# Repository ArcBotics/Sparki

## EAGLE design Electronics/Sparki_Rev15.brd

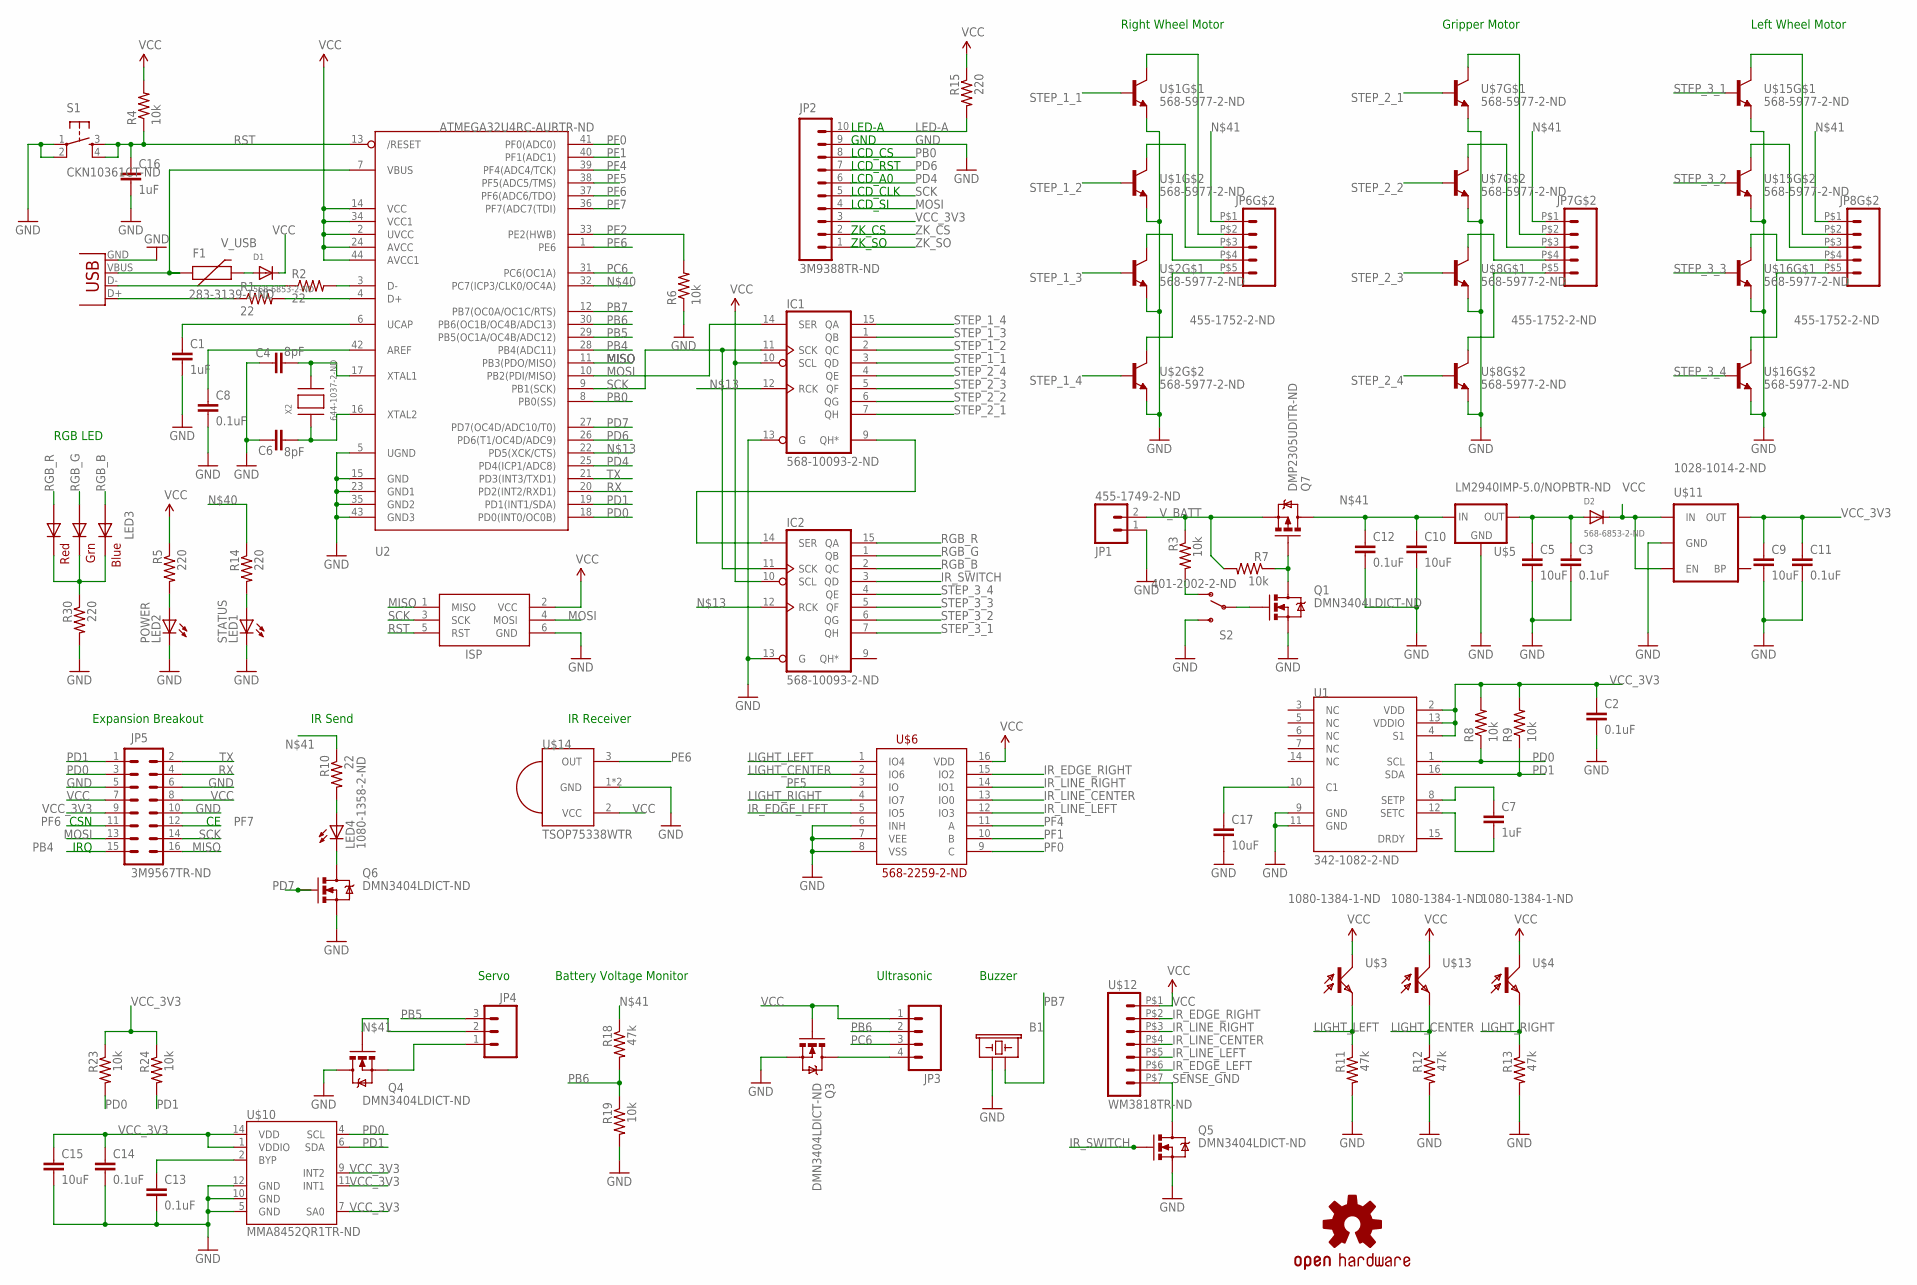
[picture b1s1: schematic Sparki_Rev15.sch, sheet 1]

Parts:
B1: SMT-0927-T-2-R; BUZZER-CCV
C1, C7, C16: 1uF; 0603-CAP
C2, C3, C8, C11, C12, C13, C14: 0.1uF; 0603-CAP
C4, C6: 8pF; 0603-CAP
C5, C9, C10, C15, C17: 10uF; 0805
D1, D2: 568-6853-2-ND; SOD-128
F1: 283-3139-1-ND; PTC-1206
IC1, IC2: 568-10093-2-ND; TSSOP16
ISP: AVRISP-6; AVRISP
JP1: 455-1749-2-ND; JST-2-SMD
JP2: 3M9388TR-ND; 1X10-2.54MM-SMD
JP3: 3M12031-ND; 1X04-2.54MM-SMD
JP4: M20-8900305-ND; 1X03_SMD_RA_MALE
JP5: 3M9567TR-ND; 2X08-2.54MM-SMD
JP6, JP7, JP8: 455-1752-2-ND; 1X05-2.0MM-JST-PH
LED1: STATUS; SML0805
LED2: POWER; SML0805
LED3: PLCC6RGBCT; RGBLED5050
LED4: 1080-1358-2-ND; FKIT-LED-1206
LOGO1: OSHW-LOGOM; OSHW-LOGO-M
Q1, Q3, Q4, Q5, Q6: DMN3404LDICT-ND; SOT23-3
Q7: DMP2305UDITR-ND; SOT23-3
R1, R2, R10: 22; 0603-RES
R3, R4, R6, R7, R8, R9, R19, R23, R24: 10k; 0603-RES
R5, R14, R15, R30: 220; 0603-RES
R11, R12, R13, R18: 47k; 0603-RES
S1: CKN10361CT-ND; TACTILE_SWITCH_SMD
S2: 401-2002-2-ND; AYZ0202
U1: 342-1082-2-ND; 16LPCC
U2: ATMEGA32U4RC-AURTR-ND; TQFP44
U$1, U$2, U$7, U$8, U$15, U$16: 568-5977-2-ND; SOT363
U$3, U$4, U$13: 1080-1384-1-ND; LED-0402
U$5: LM2940IMP-5.0/NOPBTR-ND; SOT223
U$6: 568-2259-2-ND; TSSOP-16
U$10: MMA8452QR1TR-ND; QFN-16_0.5MM
U$11: 1028-1014-2-ND; SOT23-5
U$12: WM3818TR-ND; 1X07-1.0MM-FPC
U$14: TSOP75338WTR; TSOP75338
X1: ED90342TR-ND; USB-MINIB
X2: 644-1037-2-ND; NX5032

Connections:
ACCEL_BYP: C13.1, U$10.2 (BYP)
D+: R1.2, U2.4 (D+)
D-: R2.2, U2.3 (D-)
GND: B1.- (2), C1.2, C2.2, C3.2, C4.2, C5.2, C6.2, C8.2, C9.2, C10.2, C11.2, C12.2, C13.2, C14.2, C15.2, C16.2, C17.2, IC1.8 (GND), IC1.13 (G), IC2.8 (GND), IC2.13 (G), ISP.6 (GND), JP1.1 (2), JP2.9, JP5.5, JP5.6, JP5.10, LED1.C, LED2.C, Q1.2 (S), Q3.2 (S), Q4.3 (D), Q5.2 (S), Q6.2 (S), R6.1, R11.2, R12.2, R13.2, R19.2, R30.2, S1.1, S1.2, S2.3 (S), U1.9 (GND), U1.11 (GND), U2.5 (UGND), U2.15 (GND), U2.23 (GND1), U2.35 (GND2), U2.43 (GND3), U$1.1 (E), U$1.4 (E), U$2.1 (E), U$2.4 (E), U$5.2 (GND), U$6.6 (INH), U$6.7 (VEE), U$6.8 (VSS), U$7.1 (E), U$7.4 (E), U$8.1 (E), U$8.4 (E), U$10.5 (GND), U$10.10 (GND), U$10.12 (GND), U$11.2 (GND), U$14.1 (GND), U$14.4 (GND), U$15.1 (E), U$15.4 (E), U$16.1 (E), U$16.4 (E), X1.GND
IRSEND: LED4.A, R10.2
IR_EDGE_LEFT: U$6.5 (IO5), U$12.P$6 (6); also elsewhere on the board
IR_EDGE_RIGHT: U$6.15 (IO2), U$12.P$2 (2); also elsewhere on the board
IR_LINE_CENTER: U$6.13 (IO0), U$12.P$4 (4); also elsewhere on the board
IR_LINE_LEFT: U$6.12 (IO3), U$12.P$5 (5); also elsewhere on the board
IR_LINE_RIGHT: U$6.14 (IO1), U$12.P$3 (3); also elsewhere on the board
IR_SWITCH: IC2.3 (QD), Q5.1 (G)
LED-A: JP2.10, R15.2
LIGHT_CENTER: R12.1, U$6.2 (IO6), U$13.2 (E)
LIGHT_LEFT: R11.1, U$3.2 (E), U$6.1 (IO4)
LIGHT_RIGHT: R13.1, U$4.2 (E), U$6.4 (IO7)
MISO: ISP.1 (MISO), JP5.16, U2.11 (PB3(PDO/MISO))
MOSI: IC1.14 (SER), ISP.4 (MOSI), JP2.4, JP5.13, U2.10 (PB2(PDI/MISO))
unnamed: LED2.A, R5.2
unnamed: JP7.P$2 (2), U$7.3 (C)
unnamed: R2.1, X1.D-
unnamed: R1.1, X1.D+
unnamed: Q1.3 (D), Q7.1 (G), R7.1
unnamed: JP6.P$5 (5), U$2.6 (C)
unnamed: Q1.1 (G), S2.2
unnamed: C3.1, C5.1, D2.P$2 (A), U$5.3 (OUT)
unnamed: JP6.P$4 (4), U$2.3 (C)
unnamed: JP6.P$3 (3), U$1.6 (C)
unnamed: IC1.12 (RCK), IC2.12 (RCK), U2.22 (PD5(XCK/CTS))
unnamed: JP8.P$4 (4), U$16.3 (C)
unnamed: JP8.P$3 (3), U$15.6 (C)
unnamed: JP8.P$2 (2), U$15.3 (C)
unnamed: IC1.9 (QH*), IC2.14 (SER)
unnamed: LED4.C, Q6.3 (D)
unnamed: LED1.A, R14.2
unnamed: C7.1, U1.8 (SETP)
unnamed: JP6.P$2 (2), U$1.3 (C)
unnamed: JP3.4, Q3.3 (D)
unnamed: R3.2, S2.1 (O)
unnamed: JP4.1, Q4.2 (S)
unnamed: C7.2, U1.12 (SETC)
unnamed: C17.1, U1.10 (C1)
unnamed: C8.1, U2.42 (AREF)
unnamed: JP7.P$5 (5), U$8.6 (C)
unnamed: JP7.P$4 (4), U$8.3 (C)
unnamed: JP7.P$3 (3), U$7.6 (C)
unnamed: R14.1, U2.32 (PC7(ICP3/CLK0/OC4A))
unnamed: C10.1, C12.1, JP4.2, JP6.P$1 (1), JP7.P$1 (1), JP8.P$1 (1), Q4.1 (G), Q7.3 (D), R10.1, R18.1, U$5.1 (IN)
unnamed: LED3.4 (BLUE_C), LED3.5 (RED_C), LED3.6 (GREEN_C), R30.1
unnamed: JP8.P$5 (5), U$16.6 (C)
PB0: JP2.8, U2.8 (PB0(SS))
PB4: JP5.15, U2.28 (PB4(ADC11))
PB5: JP4.3, U2.29 (PB5(OC1A/OC4B/ADC12))
PB6: JP3.2, R18.2, R19.1, U2.30 (PB6(OC1B/OC4B/ADC13))
PB7: B1.+ (1), U2.12 (PB7(OC0A/OC1C/RTS))
PC6: JP3.3, U2.31 (PC6(OC1A))
PD0: JP5.3, R8.1, R23.2, U1.1 (SCL), U2.18 (PD0(INT0/OC0B)), U$10.4 (SCL)
PD1: JP5.1, R9.1, R24.2, U1.16 (SDA), U2.19 (PD1(INT1/SDA)), U$10.6 (SDA)
PD4: JP2.6, U2.25 (PD4(ICP1/ADC8))
PD6: JP2.7, U2.26 (PD6(T1/OC4D/ADC9))
PD7: Q6.1 (G), U2.27 (PD7(OC4D/ADC10/T0))
PE2: R6.2, U2.33 (PE2(HWB))
PE6: U2.1 (PE6), U$14.3 (OUT)
PF0: U2.41 (PF0(ADC0)), U$6.9 (C)
PF1: U2.40 (PF1(ADC1)), U$6.10 (B)
PF4: U2.39 (PF4(ADC4/TCK)), U$6.11 (A)
PF5: U2.38 (PF5(ADC5/TMS)), U$6.3 (IO)
PF6: JP5.11, U2.37 (PF6(ADC6/TDO))
PF7: JP5.12, U2.36 (PF7(ADC7(TDI))
RGB_B: IC2.2 (QC), LED3.3 (BLUE_A)
RGB_G: IC2.1 (QB), LED3.1 (GREEN_A)
RGB_R: IC2.15 (QA), LED3.2 (RED_A)
RST: C16.1, ISP.5 (RST), R4.1, S1.3, S1.4, U2.13 (/RESET)
RX: JP5.4, U2.20 (PD2(INT2/RXD1))
SCK: IC1.11 (SCK), IC2.11 (SCK), ISP.3 (SCK), JP2.5, JP5.14, U2.9 (PB1(SCK))
SENSE_GND: Q5.3 (D), U$12.P$7 (7); also elsewhere on the board
STEP_1_1: IC1.3 (QD), U$1.5 (B)
STEP_1_2: IC1.2 (QC), U$1.2 (B)
STEP_1_3: IC1.1 (QB), U$2.5 (B)
STEP_1_4: IC1.15 (QA), U$2.2 (B)
STEP_2_1: IC1.7 (QH), U$7.5 (B)
STEP_2_2: IC1.6 (QG), U$7.2 (B)
STEP_2_3: IC1.5 (QF), U$8.5 (B)
STEP_2_4: IC1.4 (QE), U$8.2 (B)
STEP_3_1: IC2.7 (QH), U$15.5 (B)
STEP_3_2: IC2.6 (QG), U$15.2 (B)
STEP_3_3: IC2.5 (QF), U$16.5 (B)
STEP_3_4: IC2.4 (QE), U$16.2 (B)
TX: JP5.2, U2.21 (PD3(INT3/TXD1))
UCAP: C1.1, U2.6 (UCAP)
VBUS: F1.1, U2.7 (VBUS), X1.VBUS
VCC: D1.P$1 (C), D2.P$1 (C), IC1.10 (SCL), IC1.16 (VCC), IC2.10 (SCL), IC2.16 (VCC), ISP.2 (VCC), JP3.1, JP5.7, JP5.8, Q3.1 (G), R4.2, R5.1, R15.1, U2.2 (UVCC), U2.14 (VCC), U2.24 (AVCC), U2.34 (VCC1), U2.44 (AVCC1), U$3.1 (C), U$4.1 (C), U$6.16 (VDD), U$11.1 (IN), U$11.3 (EN), U$12.P$1 (1), U$13.1 (C), U$14.2 (VCC); also elsewhere on the board
VCC_3V3: C2.1, C9.1, C11.1, C14.1, C15.1, JP2.3, JP5.9, R8.2, R9.2, R23.1, R24.1, U1.2 (VDD), U1.4 (S1), U1.13 (VDDIO), U$10.1 (VDDIO), U$10.7 (SA0), U$10.9 (INT2), U$10.11 (INT1), U$10.14 (VDD), U$11.5 (OUT)
V_BATT: JP1.2 (1), Q7.2 (S), R3.1, R7.2
V_USB: D1.P$2 (A), F1.2
XTAL1: C4.1, U2.17 (XTAL1), X2.P$2
XTAL2: C6.1, U2.16 (XTAL2), X2.P$1
ZK_CS: JP2.2
ZK_SO: JP2.1

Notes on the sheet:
LED-A
GND
LCD_CS
LCD_RST
LCD_A0
LCD_CLK
LCD_SI
ZK_CS
ZK_SO
CSN
IRQ
Battery Voltage Monitor
Buzzer
Servo
Ultrasonic
Right Wheel Motor
Gripper Motor
Left Wheel Motor
Expansion Breakout
IR Receiver
IR Send
RGB LED

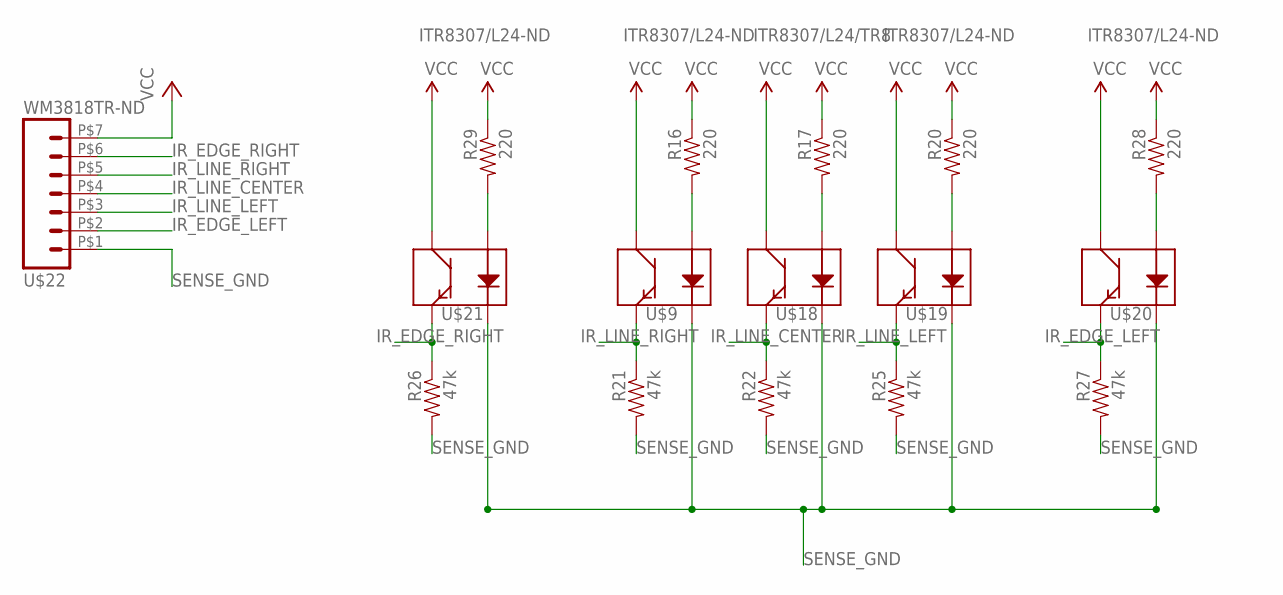
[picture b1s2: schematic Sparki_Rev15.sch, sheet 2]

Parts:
R16, R17, R20, R28, R29: 220; 0603-RES
R21, R22, R25, R26, R27: 47k; 0603-RES
U$9, U$19, U$20, U$21: ITR8307/L24-ND; QRE1113
U$18: ITR8307/L24/TR8; QRE1113
U$22: WM3818TR-ND; 1X07-1.0MM-FPC

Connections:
IR_EDGE_LEFT: R27.1, U$20.4 (E), U$22.P$2 (2); also elsewhere on the board
IR_EDGE_RIGHT: R26.1, U$21.4 (E), U$22.P$6 (6); also elsewhere on the board
IR_LINE_CENTER: R22.1, U$18.4 (E), U$22.P$4 (4); also elsewhere on the board
IR_LINE_LEFT: R25.1, U$19.4 (E), U$22.P$3 (3); also elsewhere on the board
IR_LINE_RIGHT: R21.1, U$9.4 (E), U$22.P$5 (5); also elsewhere on the board
LINEFLEDLEFT: R16.2, U$9.1 (A)
LINEFLEDMID: R17.2, U$18.1 (A)
LINEFLEDRIGHT: R20.2, U$19.1 (A)
unnamed: R28.2, U$20.1 (A)
unnamed: R29.2, U$21.1 (A)
SENSE_GND: R21.2, R22.2, R25.2, R26.2, R27.2, U$9.2 (K), U$18.2 (K), U$19.2 (K), U$20.2 (K), U$21.2 (K), U$22.P$1 (1); also elsewhere on the board
VCC: R16.1, R17.1, R20.1, R28.1, R29.1, U$9.3 (C), U$18.3 (C), U$19.3 (C), U$20.3 (C), U$21.3 (C), U$22.P$7 (7); also elsewhere on the board

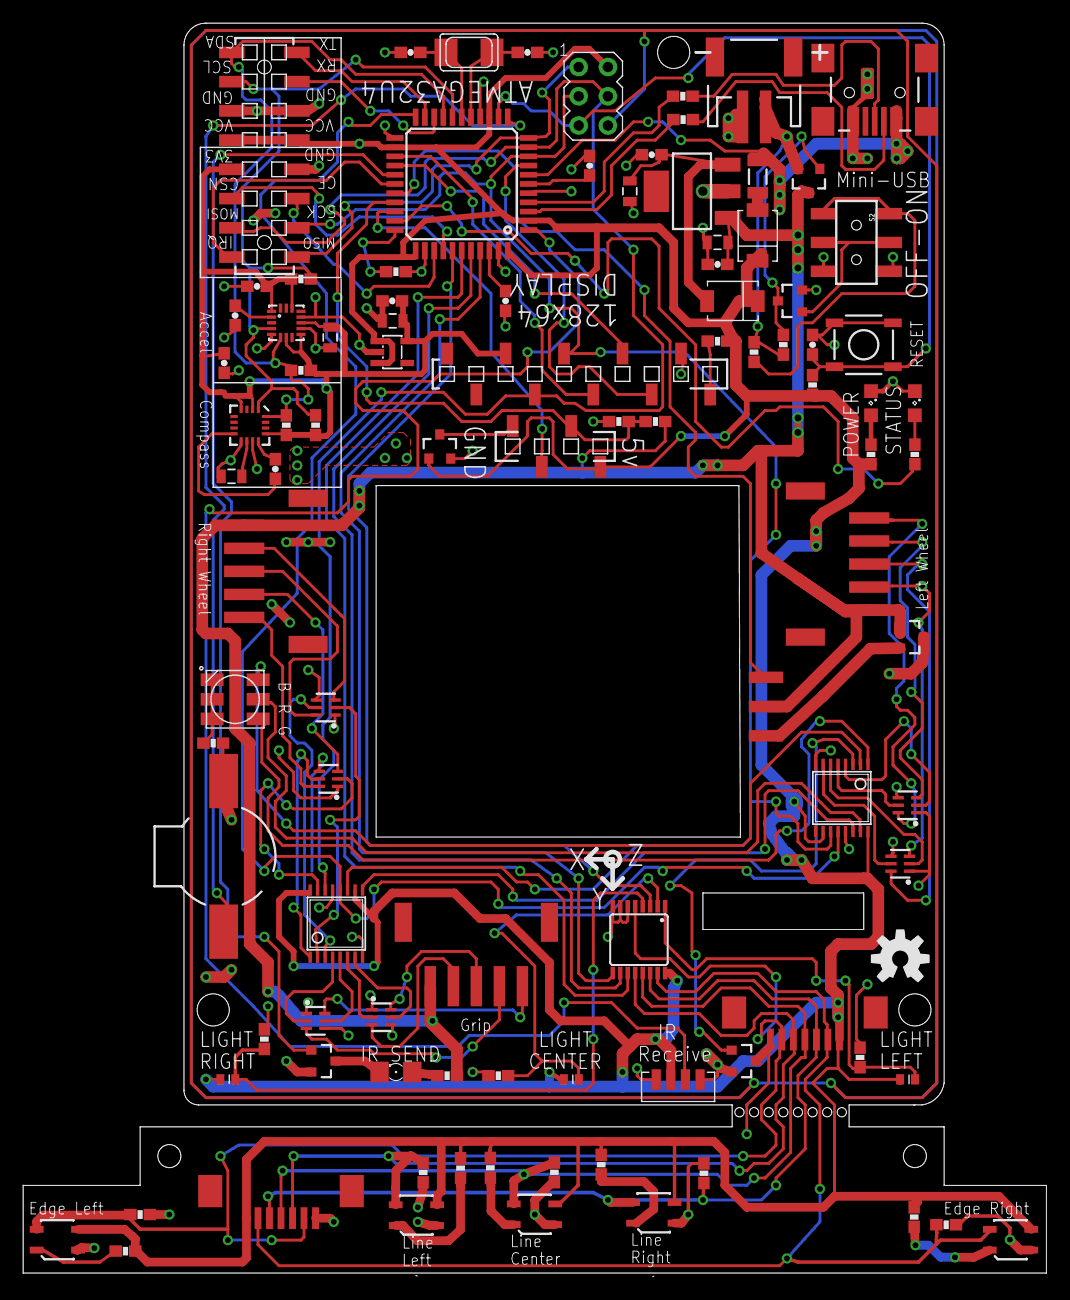
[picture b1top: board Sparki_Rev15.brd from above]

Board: 2 copper layers, 88.9 x 108.9 mm, 100 parts (0 on the bottom side), 101 nets.

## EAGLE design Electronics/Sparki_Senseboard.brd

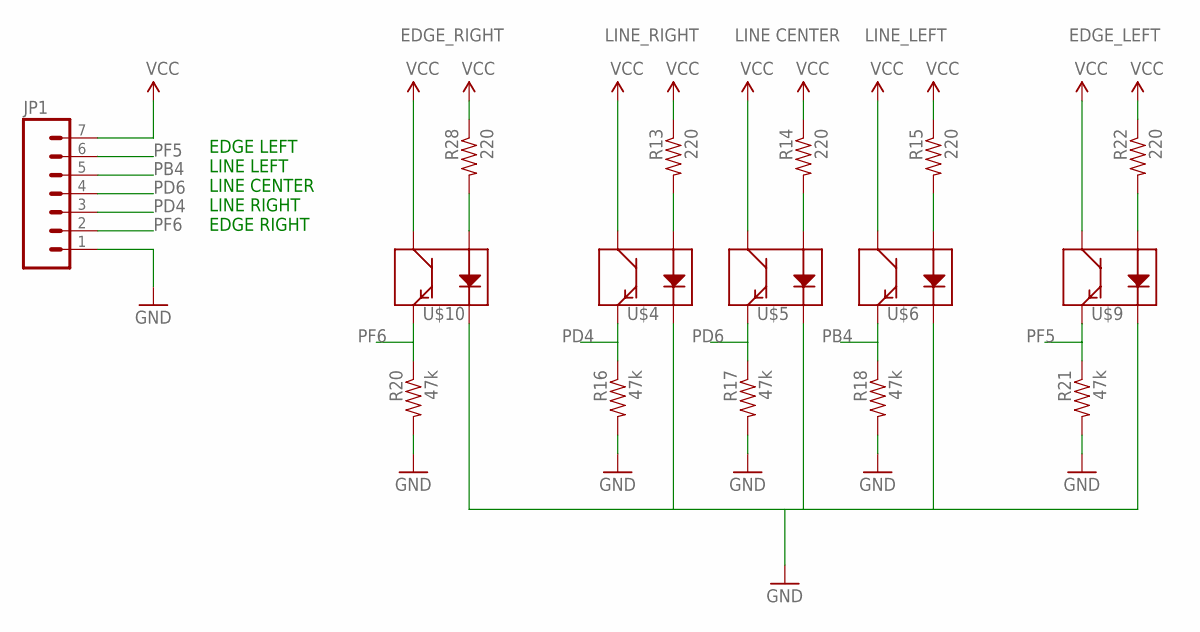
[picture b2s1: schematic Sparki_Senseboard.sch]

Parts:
JP1: M07; 1X07
R13, R14, R15, R22, R28: 220; 0603-RES
R16, R17, R18, R20, R21: 47k; 0603-RES
U$4: LINE_RIGHT; QRE1113
U$5: LINE CENTER; QRE1113
U$6: LINE_LEFT; QRE1113
U$9: EDGE_LEFT; QRE1113
U$10: EDGE_RIGHT; QRE1113

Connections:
GND: JP1.1, R16.2, R17.2, R18.2, R20.2, R21.2, U$4.2 (K), U$5.2 (K), U$6.2 (K), U$9.2 (K), U$10.2 (K)
LINEFLEDLEFT: R13.2, U$4.1 (A)
LINEFLEDMID: R14.2, U$5.1 (A)
LINEFLEDRIGHT: R15.2, U$6.1 (A)
unnamed: R28.2, U$10.1 (A)
unnamed: R22.2, U$9.1 (A)
PB4: JP1.5, R18.1, U$6.4 (E)
PD4: JP1.3, R16.1, U$4.4 (E)
PD6: JP1.4, R17.1, U$5.4 (E)
PF5: JP1.6, R21.1, U$9.4 (E)
PF6: JP1.2, R20.1, U$10.4 (E)
VCC: JP1.7, R13.1, R14.1, R15.1, R22.1, R28.1, U$4.3 (C), U$5.3 (C), U$6.3 (C), U$9.3 (C), U$10.3 (C)

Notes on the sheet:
EDGE LEFT LINE LEFT LINE CENTER LINE RIGHT EDGE RIGHT

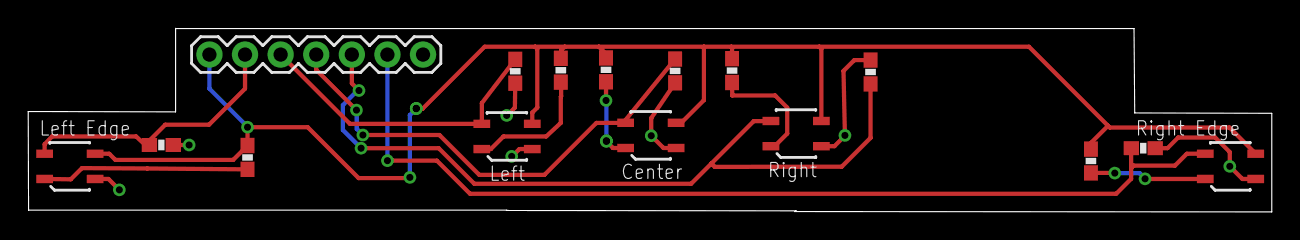
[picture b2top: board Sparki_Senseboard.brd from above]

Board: 2 copper layers, 88.7 x 13.1 mm, 16 parts (0 on the bottom side), 12 nets.

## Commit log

2013-01-31 moved arduino code to seperate folder
2013-01-31 moved arduino library files to seperate folder
2013-05-01 Updated to lastest rev
2013-05-01 added latest files
2013-06-20 Updated connectors, sensor multiplexing
2013-06-20 Removed Old Schematics
2013-07-29 Updated code partially for Rev10, no IR/Lights working
2013-07-29 Got all examples fixed and working for Rev10
2013-09-03 Fixed improper mux values for IR sensors
2013-09-03 Updated plastic files to production version
2013-09-03 removed old files
2013-09-03 Fixed error where steppers where always on
2013-09-04 updated STLs to production version
2013-09-22 Added remote control interface
2013-09-22 remove erroneous IR code correction
2013-09-22 Servo functions put on Timer1, jitter eliminated
2013-09-29 Added Display library and examples
2013-10-12 launch revision electronics
2014-02-04 Updated Arduino library and examples to current - 1.0.5.3
2014-02-04 removed unnecessary utility folder
2014-02-14 Update Hill_Climb.ino
    Corrected typo of moveBackward function.
2014-02-15 Added special meaning to 0 and -1 as move function values
2014-02-15 interrupt clear addition
2014-02-16 2x Sparki speed: Changed improper speed code
2014-02-16 Fixed hill climb example sign error
2014-02-16 Fixed line following code so it moves forward when line centered
2014-02-16 Added screen display to line following example
2014-02-16 Added default program with added edge avoidance
2014-02-16 Corrected remote example to match default code
2014-02-16 Changed edge avoidance to more reasonable value
2014-02-16 2nd though, Removed edge avoidance from default code
2014-02-17 Fixed definition error causing LCD code not to work
2014-02-17 added LCD examples
2014-02-17 Added links to part pages
2014-02-17 fixed drawPixel
2014-02-17 removed LCD drawPixel color
2014-02-17 Updated line-following example
2014-02-18 Changed error with moveRight code
2014-02-21 Add some `sei` missing after `cli`
2014-02-22 Fixed missing RGB_ from rgb color codes
2014-02-24 Moved magnetometer buffer to global array
2014-02-25 Updated RGB for more/more accurate colors. Used correct cap of 100 in the example.
2014-02-25 Changed servo min/max to keep servo from hitting LCD as often
2014-03-10 Tightened Servo Limits
2014-03-10 Allowed for negative inputs into move commands
2014-04-03 Implemented quick fixes for bugs in move*() functions
    Fixed constants in move*() functions, so driving by a specific amount of
    centimeters and turning by a specific number of degrees works correctly.
    Fixed broken code for calling move*() functions with negative arguments.
2014-04-21 Reworked motor control: provided new functions and features, but retained legacy interface
    - restructured/rewrote motor (wheel and gripper) control code
    - maintained legacy interface provided by move*() and
    gripper*() functions, but...
    - defined new functions to interface with motors
    - drive*(), spin*() and turn() for wheels
    - drive*() replaces moveForward()/moveBackward()
2014-05-13 Updated interrupt comment
    Updated comment to reflect true scheduler timing speed
2014-05-14 motion now math and step (vs time) based, changed buzzer to louder freq
2014-05-14 LCD Color Changeable
2014-05-16 IR Send function fixed and implemented
2014-05-16 Removed extraneous twi files, fixed move code
2014-05-16 Updated line-following example to not stop at start position in class pack poster
2014-05-16 Turn of IR Receive interrupt when IR Send is transmitting
2014-05-16 Roll twi.c and twi.h into SparkiWire
    Solves weird dependency/inclusion/compilation issues
2014-05-24 extraneous delay in wall avoidance example
2014-05-24 Matched remote and default code examples
2014-07-08 Added first examples for the Lessons
2014-07-09 Fixed rectangleDegrees sketch in Drawing lesson (SparkiDuino version)
2014-07-10 Fixed a small difference on the miniBloq Therenim example.
2014-07-10 Added "Moving the Robot" (SparkiDuino) examples.
2014-07-10 Added "Making Sounds" (SparkiDuino) examples.
2014-07-10 Added "First Steps with the LCD Display" (SparkiDuino) examples.
2014-07-10 Added "Using the Ultrasonic Distance Sensor" (SparkiDuino) examples.
2014-07-10 Added "Basic Gripper Usage" (SparkiDuino) examples.
2014-07-10 Added "Follow and Avoid Light" (SparkiDuino) examples.
2014-07-10 Added "Theremin" (SparkiDuino) examples.
2014-07-11 Added "Mixing Colors with the RGB LED" (miniBloq) examples.
2014-07-11 Added "Mixing Colors with the RGB LED" (SparkiDuino) examples.
2014-07-15 Added "Maze Solving" (SparkiDuino) examples.
2014-07-17 Added "Accelerometer" example.
2014-07-17 Added "Buzzer" example.
2014-07-17 Added "Gripper" example.
2014-07-17 Added "infrared LED" example.
2014-07-17 Added "Infrared Reflective Sensors" example.
2014-07-17 Added "Infrared Remote" example.
2014-07-17 Added "Infrared Remote Receiver" example.
2014-07-17 Added "Light Sensor" example.
2014-07-17 Added "Magnetometer" example.
2014-07-17 Added "RGB LED" example.
2014-07-17 Added "Status LED" example.
2014-07-17 Added "Wheels" example.
2014-07-17 Added "Servo" example.
2014-07-17 Ultrasonic" example.
2014-07-17 Ultrasonic Small Distance Test" troubleshooting code snippet.
2014-07-17 Added "Default Program" code.
2014-07-17 Added "Basic Sparki Code" code.
2014-07-17 Added "Integer Numbers" code.
2014-07-17 Added "Floating Point Numbers" code.
2014-07-18 Added "Characters" code.
2014-07-18 Added "Arrays" code.
2014-07-18 Added "Functions" code.
2014-07-18 Added "if" code.
2014-07-18 Added "switch" code.
2014-07-18 Added "while" code.
2014-07-18 Added "for" code.
2014-07-23 Added "Object Retrieval" examples.
2014-07-24 Deleted a non used "Object Retrieval" example.
2014-07-25 Advances on the "Object Mover" example.
2014-07-28 Added NO_MAG,NO_ACCEL,NO_LCD options to save memory Positioning for grippers Fixed LCD Printing Bug Added RGB Examples
2014-07-28 removed out of date remote codes
2014-07-29 EEPROM Corruption Check for servo offset
2014-07-30 Added the short loop version of the "Object Retrieval" lesson sketch.
2014-07-30 Added the zip file for the short loop version of the "Object Retrieval" lesson sketch.
2014-08-01 Added initial code snippets for the "Signal Filtering Techniques" lesson.
2014-08-04 Improved the "Average" example on the "Signal Filtering Techniques" lesson.
2014-08-04 Added the "Generic Average" example on the "Signal Filtering Techniques" lesson.
2014-08-07 Implemented battery voltage monitoring
2014-08-07 Include Radio Library + Examples
2014-08-07 Renamed RGB example to match folder
2014-08-07 Fixed Basic Radio Example
2014-08-07 Updated radio example to simplify loading
2014-08-07 Updated gripper example
2014-08-08 Added the first example for the "Computer Inputs" lesson.
2014-08-11 Added another example for the "Computer Inputs" lesson.
2014-08-11 Added the 3rd example for the "Computer Inputs" lesson.
2014-08-11 Added the 4th example for the "Computer Inputs" lesson.
2014-08-12 Added the findingHomeMark sketch for the "Room Navigation" lesson.
2014-08-12 Added the measuringRoom sketch for the "Room Navigation" lesson.
2014-08-13 Improved the measuringRoom sketch for the "Room Navigation" lesson.
2014-08-13 Added the first approach to the moveTo function for the "Room Navigation" lesson.
2014-08-20 Minor correction to the 3rd example belonging to the "Computer Inputs" lesson.
2014-08-28 Added the first Android example fro the "Sparki + Android" lesson.
2014-08-31 Added more example programs for the "Sparki + Android" lesson
2014-08-31 Added new "Computer Inputs" lesson example.
2014-08-31 Added new example for the "Sparki + Android: Multipl Sensors" lesson.
2014-08-31 Add .apk file for the 3rd Sparki+Android example
2014-09-01 Corrected a small typo in the moveTo example from the "Room Navigation" lesson.
2014-09-01 Added the generic dead reckoning example moveTo1 for the "Room Navigation" lesson.
2014-09-08 Fixed negative movement looping
2014-09-12 Added the returnHomeTest example for the "Room Navigation" lesson.
2014-09-12 Worked on the doors0 example for the "Room Navigation" lesson.
2014-09-12 Resised code on some examples for the "Room Navigation" lesson.
2014-09-15 Worked on the doors0 example: problems with the error in the ultrasonic ranger.
2014-09-15 Started to work on the deadReckoningNav0 example: problems with the error in the ultrasonic ranger.
2014-09-15 Started to work on the deadReckoningNav0 example.
2014-09-15 Worked on the deadReckoningNav0 example for the "Room Navigation" lesson.
2014-09-15 Continued working on the deadReckoningNav0 example for the "Room Navigation" lesson.
2014-11-30 Added compatibility function for old motorRotate
2014-12-15 Fixed compatability function
2015-03-05 created .gitignore file and lesson plans folder
2015-05-01 Maze_Completing_01
    Added for new maze solving material
2015-05-14 Rename to basic_code to basics, new arduino req
2015-05-14 added const to progmem variables
2015-05-14 added const to progmem
2015-05-28 New Maze Solving Arduino files
    Arduino files for maze solving (not line following)
    mazeSolver01 - partial
    mazeSolver02 - full
2015-06-09 Advanced Bluetooth Section Code for Sparki
    Code to accept forward/left/right/stop commands via bluetooth added
2015-06-09 Fixed Names
    Fixed names to be consistent with previous naming format
2015-06-10 more bluetooth code
    Bluetooth code for advanced, multi word parsing
2015-06-11 Update movement02 in bluetooth
    Backtracked a minor amount, had to change code
2015-06-11 Movement02 code changed again
2015-06-11 Code change movement02
2015-06-11 Bluetooth/movement conflict
    When I add a movement function I start getting very strange things
    happening, serial ports disappear, a println appeared to not copy
    correctly to the Atmega, the code which previously worked (and was not
    changed) no longer functions. Details in email to Joe.
    TLDR- bluetoothMovement02 works fine. bluetoothMovement02FAIL does not.
    It doesn’t even get to the code that was added because somehow the code
2015-06-11 More bluetooth code
    Finishing this up and scaling down scope of lesson to account for
    issues encountered
2015-06-13 Last bit of Bluetooth/Serial comm related code
2015-06-15 Sparki LCD Eyes and Movement Code
2015-06-15 naming convention style correction
2015-06-25 Droid bluetooth file
    adding droid bluetooth file
    Almost the same as regular bluetooth movement files
2015-06-28 Changed variable to PC name
2015-06-28 zip file for PC variable name
2015-06-30 Changed floating numbers sketch
    Changed code so it doesn’t allude to profanity
2015-06-30 Code for scrolling through all char values
2015-07-01 Search through array example code
2015-07-01 Changing null position
2015-07-08 Second while loop example code
2015-07-08 Recap while code
2015-11-19 Improvements made to LCD code, additions for new LCD
2015-12-11 Updated Library examples to Arduino 1.6 standards
2015-12-11 Added Sparki Ardublock
2015-12-12 NO_LCD now still loads Sparki logo from progmem, bypassing RAM
2015-12-13 reverted from testing for large LCD
2015-12-13 updated version numbers to avoid library update interferance
2016-03-17 ensure pitches.h is included
2016-03-25 Fixed I2C initialization for Accel and Mag
2016-04-29 Fixed bug in pixel color writing - Thanks Jermey!
2016-05-18 fixed LCD update masking error - Thanks Nikolaus Correll!
2016-07-06 Fixed buffer overflow error caused by multiple simultaneous remotes
2018-03-06 Added ArduBlock LCD features, updated to latest version
    Fixed incompatibilities in Ardublock caused by latest version of
    Arduino by updating Ardublock to latest version, added in LCD usage
    while I was at it

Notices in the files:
parts and their libraries:
SparkFun-Passives: Licensing: CC v3.0 Share-Alike You are welcome to use this library for commercial purposes.
